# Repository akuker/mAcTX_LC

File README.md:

# mAcTX_LC
Adapter to use an ATX power supply with a Macintosh LC series computer

# Background
These files were originally developed by blusnowkitty on the 68kMLA forum. They are being archived here so that the community can make updates/changes/improvements as needed and to provide a location for documentation and assembly instructions.
https://68kmla.org/bb/index.php?threads/mactx-lc-boards.38912/

```
Once again, here's the mAcTX LC KiCad project. Public domain, do whatever, yadda yadda; I just ask 
that you don't use the mAcTX name if you use this in your own project and don't sell for profit. 
This only covers the LC version as the mAcTX IIc is owned by compgeke and it's his choice if he
wants to open-source, public domain, or keep the files private.
```

Note: As of 06-Apr-2023, bluesnowkitty has updated the post with the following:

```
Alex Perez has reached out to me seeking permission to sell the design on his store, Rabbit Hole 
Computing. I have authorized him to sell the mAcTX LC and use the mAcTX LC name for the product. 
You are, of course, still free to download the design and make your own adaptations as you see fit; 
I will no longer enforce the "Don't sell for profit" clause in my OP.

Compgeke's mAcTX IIc will also be making an appearance on Rabbit Hole Computing, but it will still
be Compgeke's choice if he wants to release the project files to the public.
```

## Overview of mAcTX_LC

## Pictures

Some images from the [68kmla forums](https://68kmla.org/bb/index.php?threads/mactx-atx-to-classic-macs.34492):

# Bill of Materials

## Version 1.3 Bill of Materials

| Reference | Description         | Digikey | Mouser  |
| --------- | ------------------- |--------- | ------- |
| R1        | 10k Resistor | [PR01000101002JR500](https://www.digikey.com/en/products/detail/vishay-beyschlag-draloric-bc-components/PR01000101002JR500/595971)   |  TBD  |
| R2        | 10k Resistor | [PR01000101002JR500](https://www.digikey.com/en/products/detail/vishay-beyschlag-draloric-bc-components/PR01000101002JR500/595971)   |  TBD  |
| C1        | 10uF Capacitor      | [Rubycon 100YXF10MEFC6.3X11](https://www.digikey.com/en/products/detail/rubycon/100YXF10MEFC6-3X11/3563099)   |  TBD  |
| C2        | 10uF Capacitor      |  [Rubycon 100YXF10MEFC6.3X11](https://www.digikey.com/en/products/detail/rubycon/100YXF10MEFC6-3X11/3563099)   |  TBD  |
| J1        | ATX Power Connector |  [Molex 39-28-8240](https://www.digikey.com/en/products/detail/molex/0039288240/930307?s=N4IgTCBcDaIKwGYAcBaBBOFZVLAFgAYQBdAXyA)| [Molex 39-28-8240](https://www.mouser.com/ProductDetail/538-39-28-8240) |
| U1        | Max660 Charge Pump  |  [LMC7660IM-NOPB](https://www.digikey.com/en/products/detail/texas-instruments/LMC7660IM-NOPB/308019)|  TBD  |

**NOTE: THESE COMPONENTS HAVE NOT BEEN VALIDATED!!! ORDER THESE AT YOUR OWN RISK**

## Version 2.0 Bill of Materials

| Reference | Description         | LCSC |
| --------- | ------------------- |--------- |
| R1        | 10k Resistor | C17903  |
| R2        | 10k Resistor Value| C17903  |
| C1        | 10uF Capacitor      |  C72485 |
| C2        | 10uF Capacitor      |  C72485 |
| J1        | ATX Power Connector |  TBD |
| U1        | Max660 Charge Pump  |  C434489 |

**NOTE: THESE COMPONENTS HAVE NOT BEEN VALIDATED!!! ORDER THESE AT YOUR OWN RISK**

## Other part numbers
https://tinkerdifferent.com/threads/macintosh-connector-part-numbers.135/

* LC Style Power Supply Connector: Molex KK396 [(source: TinkerDifferent)](https://tinkerdifferent.com/threads/macintosh-connector-part-numbers.135/)

# Board

## Version 1.3
[Version 1.3 Schematic](https://github.com/akuker/mAcTX_LC/blob/main/KiCad/mactxlc_sch.pdf)

## Version 2.0

# Assembly instructions

* TBD

# Other versions

Androda (https://androda.work/) is making a follow-on project called The LC MACAA Power Supply. Watch https://androda.work/shop/ for updates.

# Connector notes

* [Molex KK396 Series Datasheet](https://www.digikey.com/htmldatasheets/production/2998981/0/0/1/08-50-Prod-Spec.pdf)
* [Molex KK Series Overview](http://www.literature.molex.com/SQLImages/kelmscott/Molex/PDF_Images/987650-9819.pdf)
* [KK396 Product Overview](https://www.content.molex.com/dxdam/literature/987651-0405.pdf)

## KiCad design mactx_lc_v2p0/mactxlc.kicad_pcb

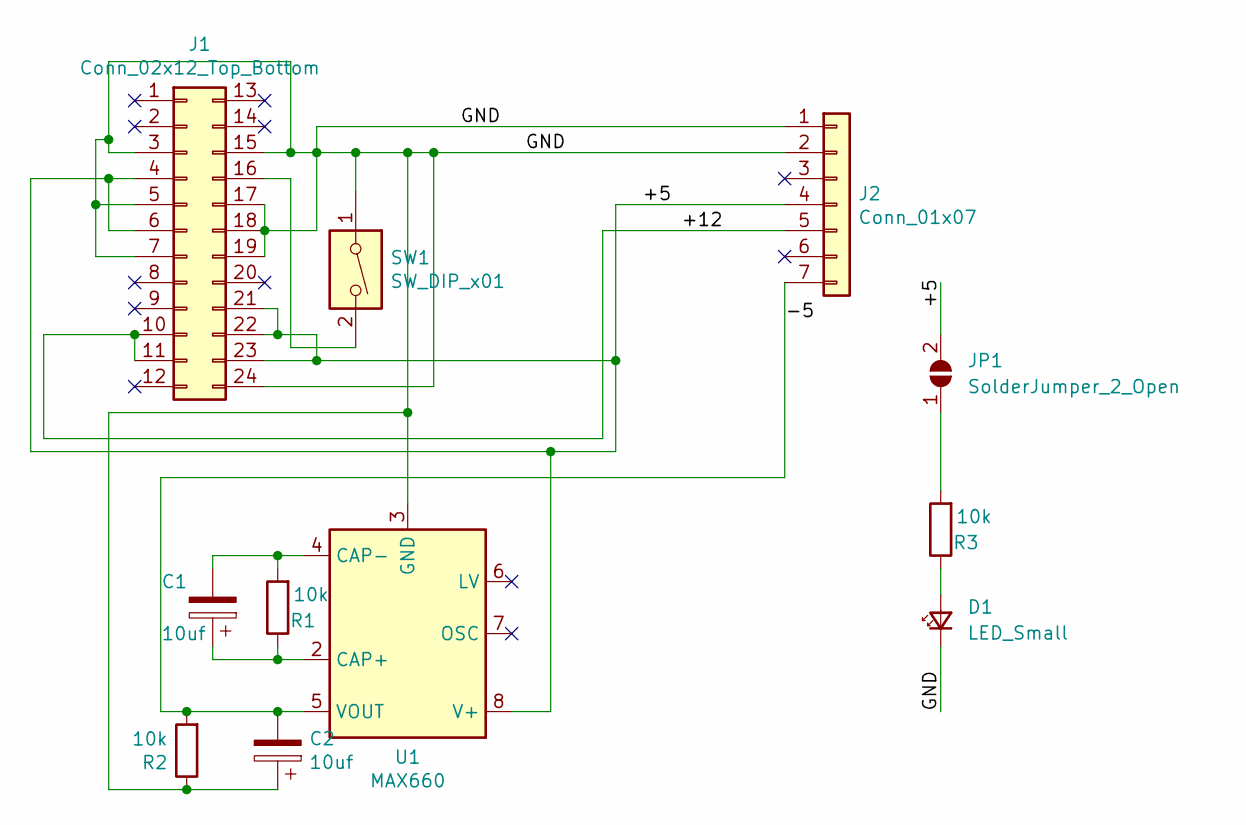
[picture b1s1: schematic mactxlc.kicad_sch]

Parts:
C1, C2: 10uf; C_Elec_4x5.4; LCSC C72485
D1: LED_Small; LED_0805_2012Metric; LCSC C2297
J1: Conn_02x12_Top_Bottom; Molex_Mini-Fit_Jr_5566-24A_2x12_P4.20mm_Vertical
J2: Conn_01x07; Molex_KK-396_A-41791-0007_1x07_P3.96mm_Vertical
JP1: SolderJumper_2_Open; SolderJumper-2_P1.3mm_Open_RoundedPad1.0x1.5mm
R1, R2, R3: 10k; R_0805_2012Metric; LCSC C17414
SW1: SW_DIP_x01; PinHeader_1x02_P2.54mm_Vertical
U1: MAX660; SOP-8_3.9x4.9mm_P1.27mm; LCSC C434489

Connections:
/+5: J1.4, J1.6, J1.21, J1.22, J1.23, J2.4, JP1.2 (B), U1.8 (V+)
/+12: J1.10, J1.11, J2.5
/-5: C2.2, J2.7, R2.2, U1.5 (VOUT)
/GND: C2.1, D1.1 (K), J1.3, J1.5, J1.7, J1.15, J1.17, J1.18, J1.19, J1.24, J2.1, J2.2, R2.1, SW1.1, U1.3 (GND)
unnamed: C1.1, R1.1, U1.2 (CAP+)
unnamed: C1.2, R1.2, U1.4 (CAP-)
unnamed: D1.2 (A), R3.1
unnamed: J1.16, SW1.2
unnamed: JP1.1 (A), R3.2

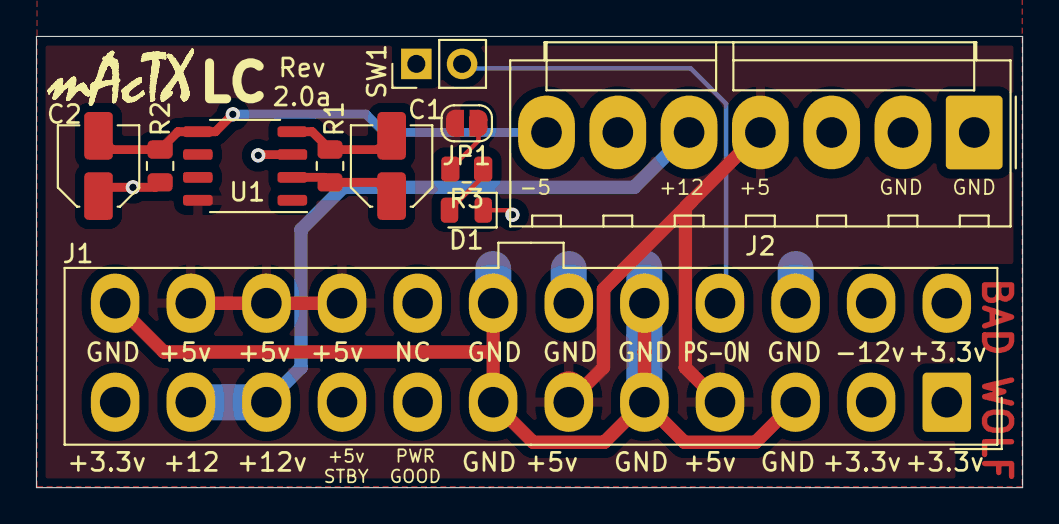
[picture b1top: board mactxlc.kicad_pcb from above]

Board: 2 copper layers, 54.8 x 25.1 mm, 11 parts (0 on the bottom side), 9 nets.

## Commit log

2022-02-01 Initial files from blusnokitty https://68kmla.org/bb/index.php?threads/mactx-lc-boards.38912/
2022-02-01 Updated license and readme to give credit to blusnowkitty
2022-02-01 Update README.md
    Cleanup formatting
2022-02-01 Update README.md
    Added some components to the BOM
2022-02-12 Add PDF of schematic and board pics
2022-02-12 Resized image
2022-02-20 Updated to KiCad 6 and silkscreen updates
2022-02-20 Initial version of mAcTX LC 2.0
2022-02-20 Pictures from the 68kmla forum thread https://68kmla.org/bb/index.php?threads/mactx-atx-to-classic-macs.34492/
2022-02-20 Renamed folder
2022-02-21 Fixed LC power connector and resistor part number
